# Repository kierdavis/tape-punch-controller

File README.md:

# Tape Punch Controller

This repository contains the source code and CAD designs used for my university third year individual project.

The project involves designing a system that can interface a restored [Teletype BPRE-type High Speed Tape Punch][tapepunch] to a modern computer over USB.

## Repository Layout

- [`/firmware`][repo-firmware]: source code of the firmware running on the microcontroller
- [`/pcb`][repo-pcb]: design files for the PCB used in the device
- [`/mechanical`][repo-mechanical]: design files for various laser-cut parts

[tapepunch]: http://www.computinghistory.org.uk/det/2312/teletype-brpe-20-high-speed-tape-punch/
[repo-firmware]: https://github.com/kierdavis/tape-punch-controller/tree/master/firmware
[repo-pcb]: https://github.com/kierdavis/tape-punch-controller/tree/master/pcb
[repo-mechanical]: https://github.com/kierdavis/tape-punch-controller/tree/master/mechanical

## Branches

Two main Git branches are used with this repository: `master` and `stable`. New development occurs on `master`; when it has been tested and is deemed ready to ship to the client, it is merged into `stable`. `stable` should be a reflection of the version currently in use by the client.

## License

The contents of this repository are licensed under the terms of the MIT license. See the [LICENSE](LICENSE) file for more details.

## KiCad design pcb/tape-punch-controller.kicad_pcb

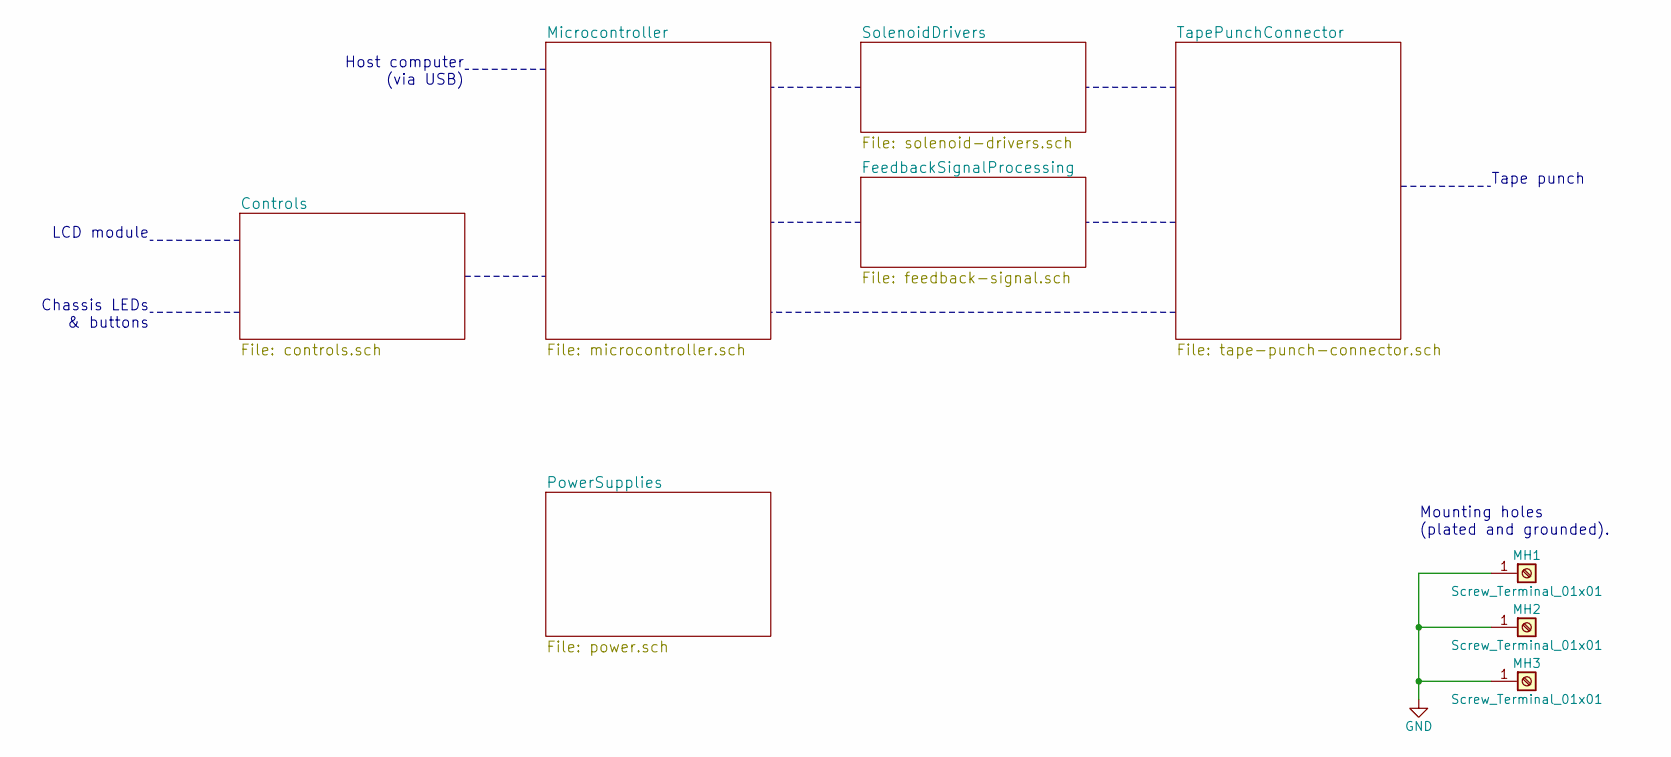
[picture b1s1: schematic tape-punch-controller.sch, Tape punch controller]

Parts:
MH1, MH2, MH3: Screw_Terminal_01x01; MountingHole_4.3mm_M4_Pad

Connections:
GND: MH1.1, MH2.1, MH3.1; also elsewhere on the board

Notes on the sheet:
Mounting holes (plated and grounded).
LCD module
Chassis LEDs & buttons
Host computer (via USB)
Tape punch

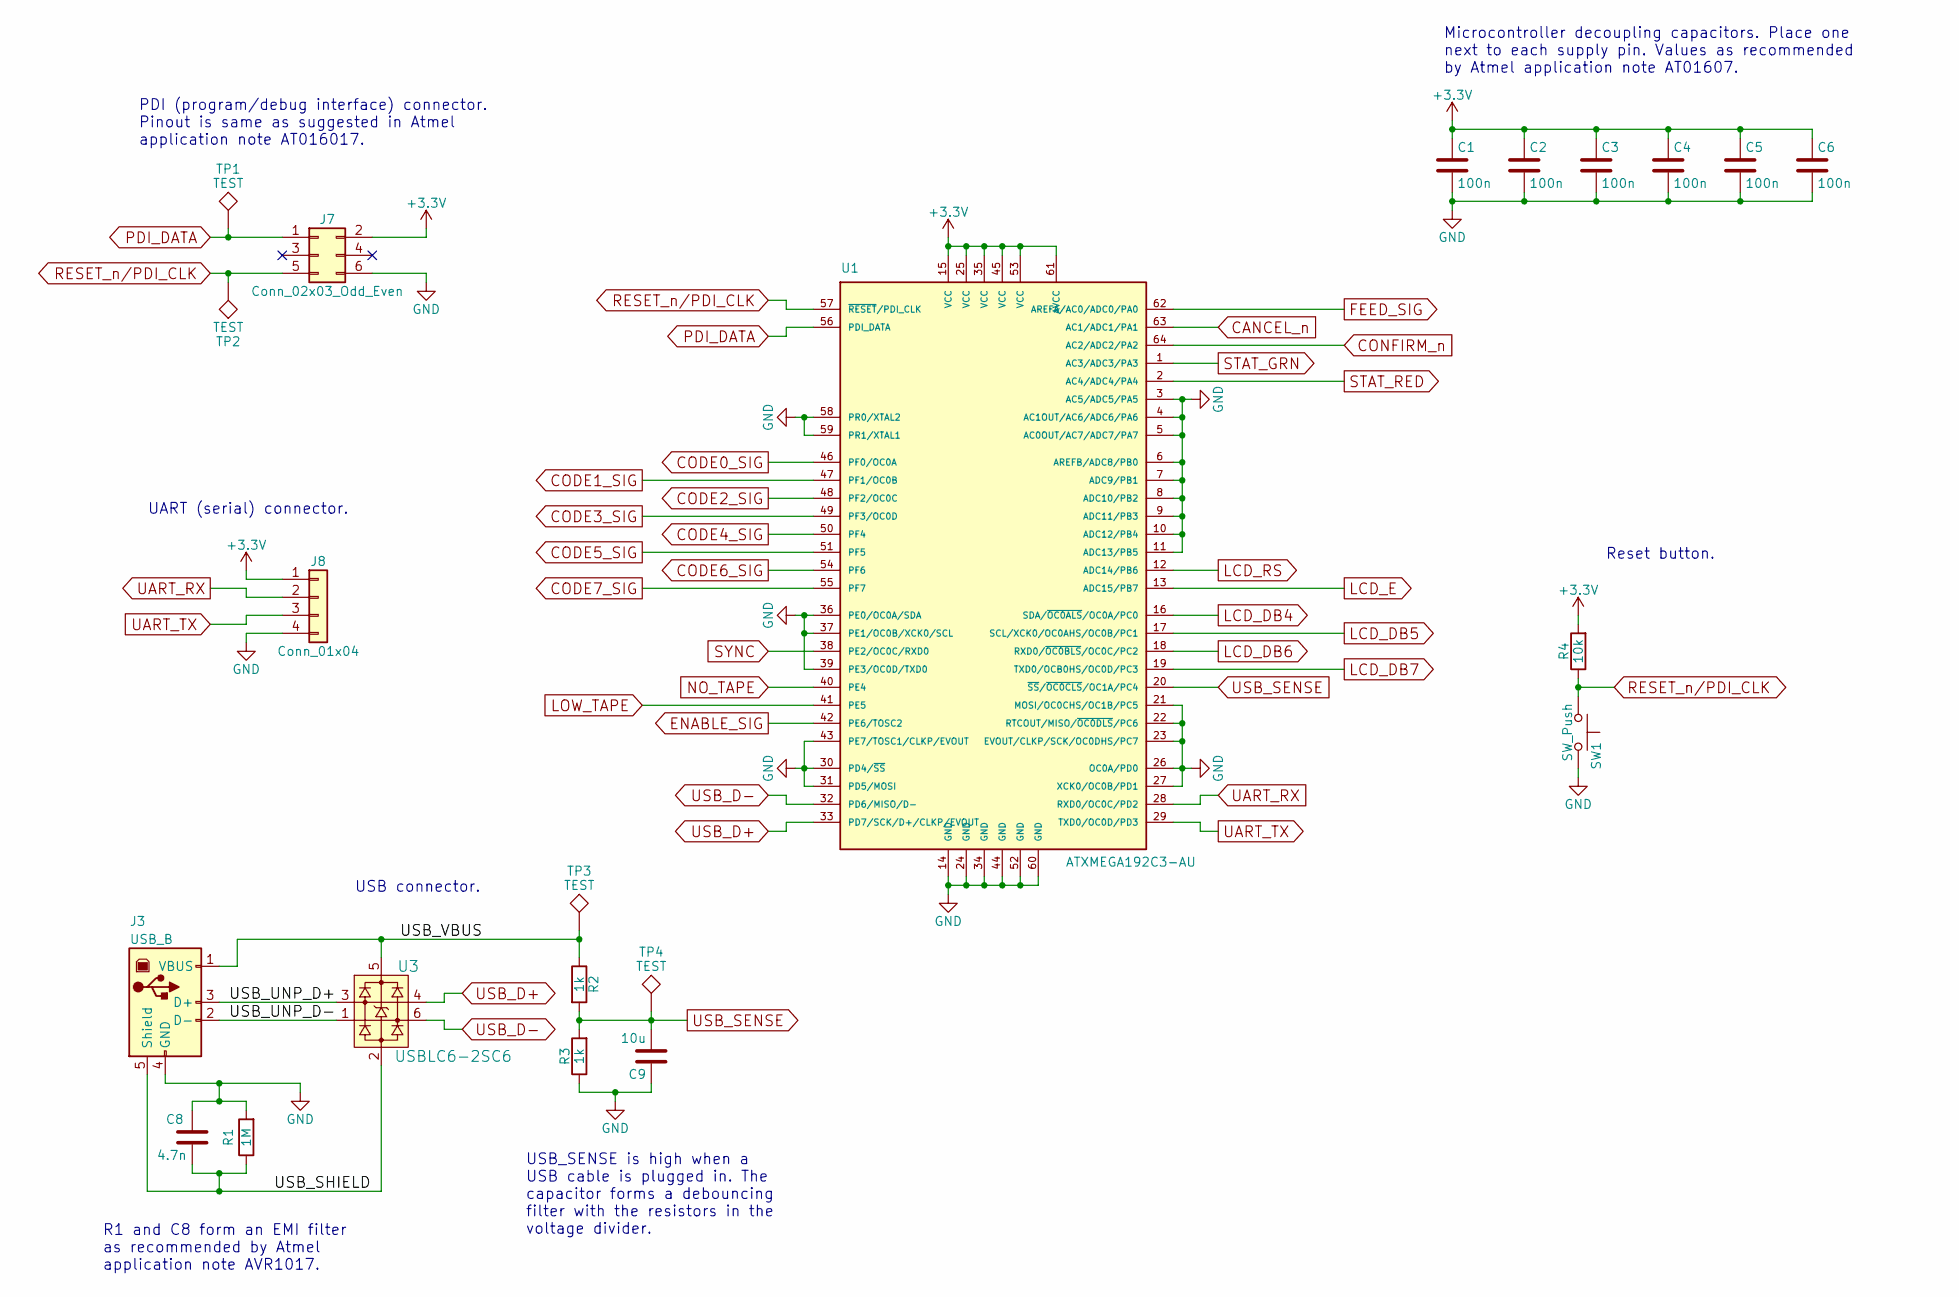
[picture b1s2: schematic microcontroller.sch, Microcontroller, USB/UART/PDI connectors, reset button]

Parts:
C1, C2, C3, C4, C5, C6: 100n; C_0805_HandSoldering
C8: 4.7n; C_0805_HandSoldering
C9: 10u; C_1206_HandSoldering
J3: USB_B; Multicomp_MC32597
J7: Conn_02x03_Odd_Even; Pin_Header_Straight_2x03_Pitch2.54mm
J8: Conn_01x04; Pin_Header_Straight_1x04_Pitch2.54mm
R1: 1M; R_0805_HandSoldering
R2, R3: 1k; R_0805_HandSoldering
R4: 10k; R_0805_HandSoldering
SW1: SW_Push; SW_Tactile_SPST_Angled_PTS645Vx58-2LFS
TP1, TP2, TP3, TP4: TEST; Measurement_Point_Round-SMD-Pad_Small
U1: ATXMEGA192C3-AU; TQFP-64_14x14mm_Pitch0.8mm
U3: USBLC6-2SC6; SOT-23-6_Handsoldering

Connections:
+3V3: C1.1, C2.1, C3.1, C4.1, C5.1, C6.1, J7.2, J8.1, R4.2, U1.15 (VCC), U1.25 (VCC), U1.35 (VCC), U1.45 (VCC), U1.53 (VCC), U1.61 (AVCC); also elsewhere on the board
/Microcontroller/USB_SHIELD: C8.2, J3.5 (Shield), R1.1, U3.2 (GND)
/Microcontroller/USB_UNP_D+: J3.3 (D+), U3.3 (D+)
/Microcontroller/USB_UNP_D-: J3.2 (D-), U3.1 (D-)
/Microcontroller/USB_VBUS: J3.1 (VBUS), R2.1, TP3.1, U3.5 (VBUS)
CANCEL_n: U1.63 (AC1/ADC1/PA1); also elsewhere on the board
CODE0_SIG: U1.46 (PF0/OC0A); also elsewhere on the board
CODE1_SIG: U1.47 (PF1/OC0B); also elsewhere on the board
CODE2_SIG: U1.48 (PF2/OC0C); also elsewhere on the board
CODE3_SIG: U1.49 (PF3/OC0D); also elsewhere on the board
CODE4_SIG: U1.50 (PF4); also elsewhere on the board
CODE5_SIG: U1.51 (PF5); also elsewhere on the board
CODE6_SIG: U1.54 (PF6); also elsewhere on the board
CODE7_SIG: U1.55 (PF7); also elsewhere on the board
CONFIRM_n: U1.64 (AC2/ADC2/PA2); also elsewhere on the board
ENABLE_SIG: U1.42 (PE6/TOSC2); also elsewhere on the board
FEED_SIG: U1.62 (AREFA/AC0/ADC0/PA0); also elsewhere on the board
GND: C1.2, C2.2, C3.2, C4.2, C5.2, C6.2, C8.1, C9.1, J3.4 (GND), J7.6, J8.4, R1.2, R3.1, SW1.2, U1.3 (AC5/ADC5/PA5), U1.4 (AC1OUT/AC6/ADC6/PA6), U1.5 (AC0OUT/AC7/ADC7/PA7), U1.6 (AREFB/ADC8/PB0), U1.7 (ADC9/PB1), U1.8 (ADC10/PB2), U1.9 (ADC11/PB3), U1.10 (ADC12/PB4), U1.11 (ADC13/PB5), U1.14 (GND), U1.21 (MOSI/OC0CHS/OC1B/PC5), U1.22 (RTCOUT/MISO/~OC0DLS~/PC6), U1.23 (EVOUT/CLKP/SCK/OC0DHS/PC7), U1.24 (GND), U1.26 (OC0A/PD0), U1.27 (XCK0/OC0B/PD1), U1.30 (PD4/~SS~), U1.31 (PD5/MOSI), U1.34 (GND), U1.36 (PE0/OC0A/SDA), U1.37 (PE1/OC0B/XCK0/SCL), U1.39 (PE3/OC0D/TXD0), U1.43 (PE7/TOSC1/CLKP/EVOUT), U1.44 (GND), U1.52 (GND), U1.58 (PR0/XTAL2), U1.59 (PR1/XTAL1), U1.60 (GND); also elsewhere on the board
LCD_DB4: U1.16 (SDA/~OC0ALS~/OC0A/PC0); also elsewhere on the board
LCD_DB5: U1.17 (SCL/XCK0/OC0AHS/OC0B/PC1); also elsewhere on the board
LCD_DB6: U1.18 (RXD0/~OC0BLS~/OC0C/PC2); also elsewhere on the board
LCD_DB7: U1.19 (TXD0/OCB0HS/OC0D/PC3); also elsewhere on the board
LCD_E: U1.13 (ADC15/PB7); also elsewhere on the board
LCD_RS: U1.12 (ADC14/PB6); also elsewhere on the board
LOW_TAPE: U1.41 (PE5); also elsewhere on the board
NO_TAPE: U1.40 (PE4); also elsewhere on the board
PDI_DATA: J7.1, TP1.1, U1.56 (PDI_DATA)
RESET_n/PDI_CLK: J7.5, R4.1, SW1.1, TP2.1, U1.57 (~RESET~/PDI_CLK)
STAT_GRN: U1.1 (AC3/ADC3/PA3); also elsewhere on the board
STAT_RED: U1.2 (AC4/ADC4/PA4); also elsewhere on the board
SYNC: U1.38 (PE2/OC0C/RXD0); also elsewhere on the board
UART_RX: J8.2, U1.28 (RXD0/OC0C/PD2)
UART_TX: J8.3, U1.29 (TXD0/OC0D/PD3)
USB_D+: U1.33 (PD7/SCK/D+/CLKP/EVOUT), U3.4 (D+)
USB_D-: U1.32 (PD6/MISO/D-), U3.6 (D-)
USB_SENSE: C9.2, R2.2, R3.2, TP4.1, U1.20 (~SS~/~OC0CLS~/OC1A/PC4)

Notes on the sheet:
Microcontroller decoupling capacitors. Place one next to each supply pin. Values as recommended by Atmel application note AT01607.
UART (serial) connector.
PDI (program/debug interface) connector. Pinout is same as suggested in Atmel application note AT016017.
USB connector.
USB_SENSE is high when a USB cable is plugged in. The capacitor forms a debouncing filter with the resistors in the voltage divider.
R1 and C8 form an EMI filter as recommended by Atmel application note AVR1017.
Reset button.

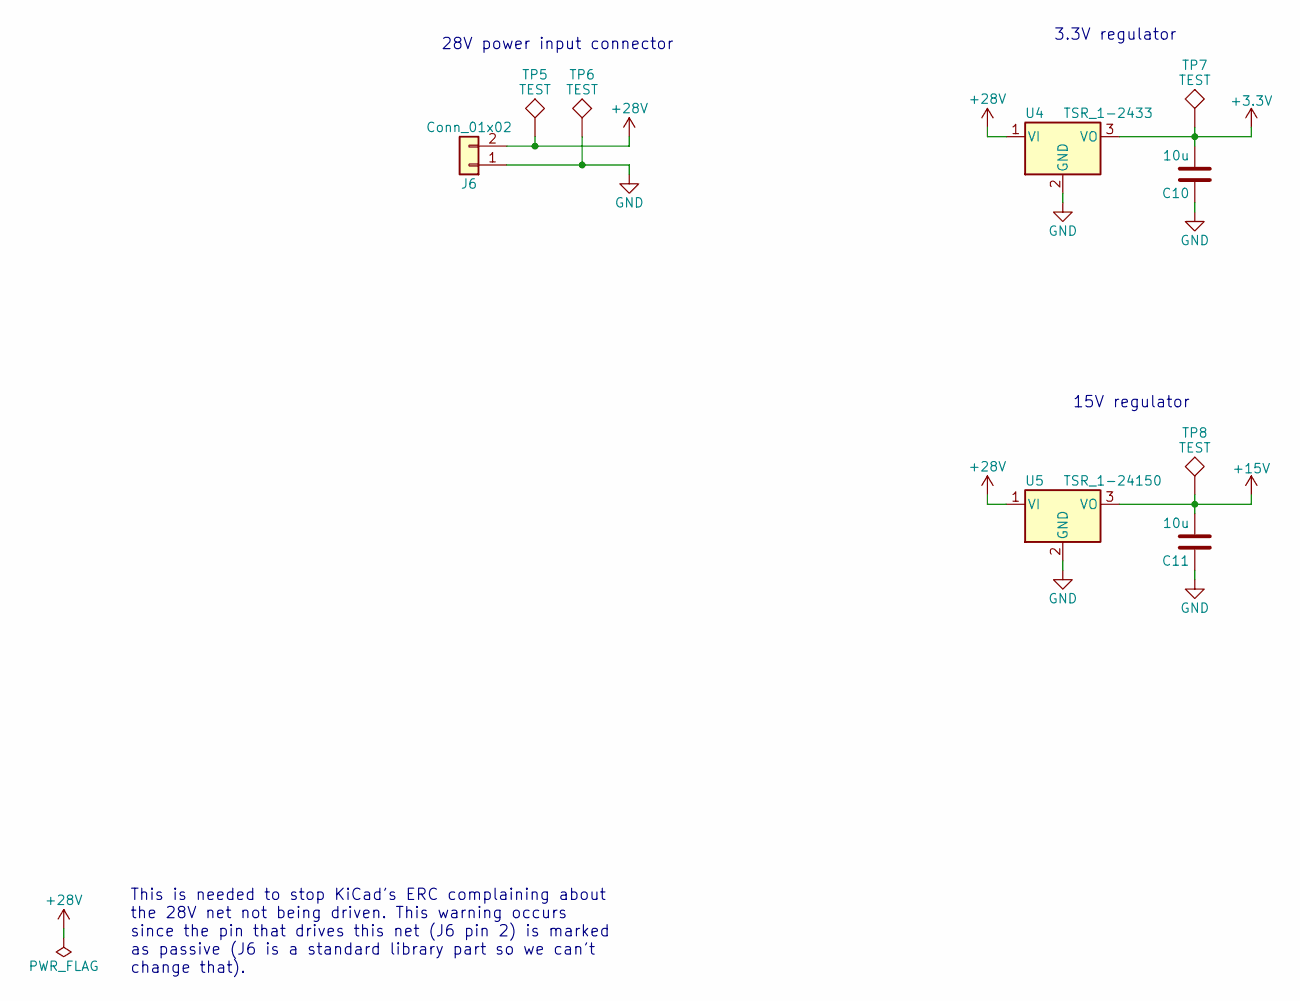
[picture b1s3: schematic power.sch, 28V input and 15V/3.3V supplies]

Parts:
C10, C11: 10u; C_1206_HandSoldering
J6: Conn_01x02; Multicomp_MC000048
TP5, TP6, TP7, TP8: TEST; Measurement_Point_Round-SMD-Pad_Small
U4: TSR_1-2433; TO-220-3_Vertical
U5: TSR_1-24150; TO-220-3_Vertical

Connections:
+3V3: C10.2, TP7.1, U4.3 (VO); also elsewhere on the board
+15V: C11.2, TP8.1, U5.3 (VO); also elsewhere on the board
+28V: J6.2, TP5.1, U4.1 (VI), U5.1 (VI); also elsewhere on the board
GND: C10.1, C11.1, J6.1, TP6.1, U4.2 (GND), U5.2 (GND); also elsewhere on the board

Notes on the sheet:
28V power input connector
3.3V regulator
15V regulator
This is needed to stop KiCad's ERC complaining about the 28V net not being driven. This warning occurs since the pin that drives this net (J6 pin 2) is marked as passive (J6 is a standard library part so we can't change that).

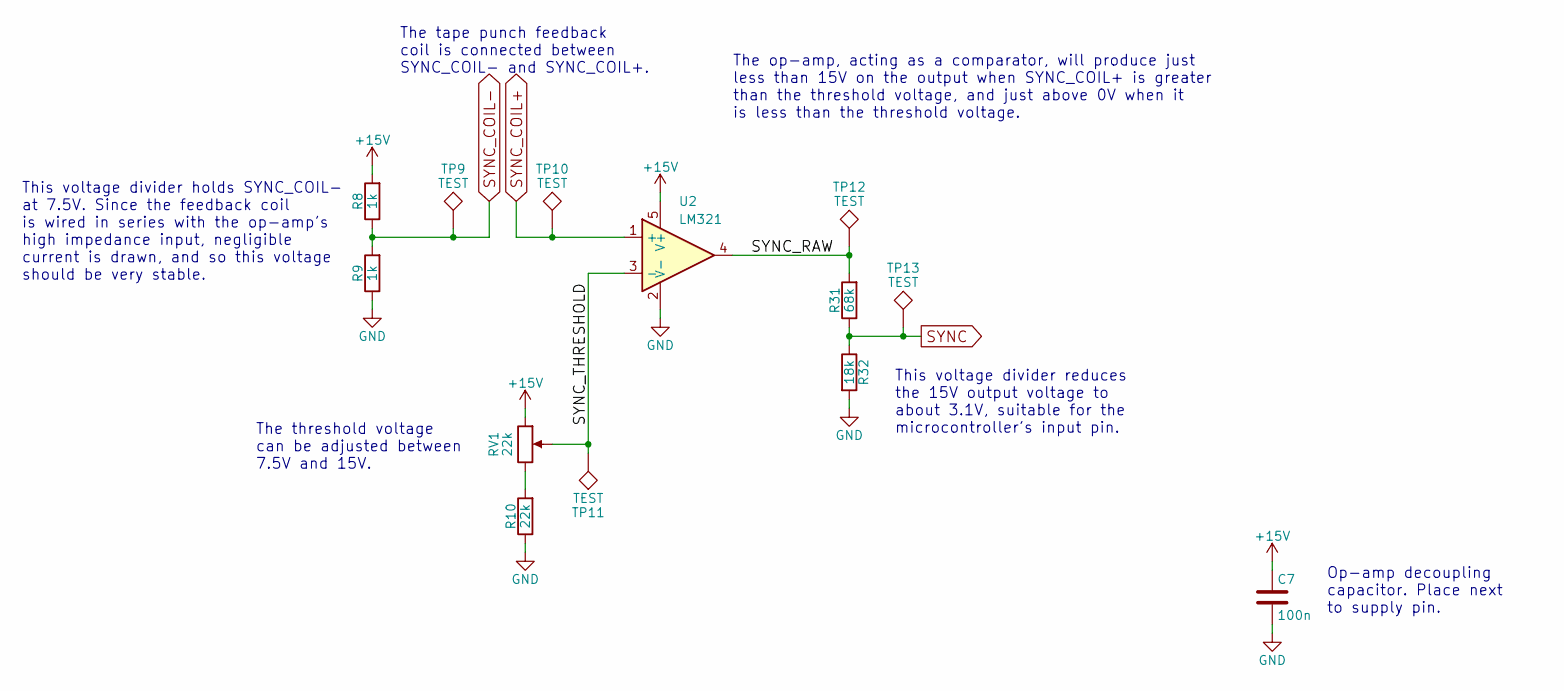
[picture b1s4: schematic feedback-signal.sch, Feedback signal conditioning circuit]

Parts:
C7: 100n; C_0805_HandSoldering
R8, R9: 1k; R_0805_HandSoldering
R10: 22k; R_0805_HandSoldering
R31: 68k; R_0805_HandSoldering
R32: 18k; R_0805_HandSoldering
RV1: 22k; Citec_CB10LV103M
TP9, TP10, TP11, TP12, TP13: TEST; Measurement_Point_Round-SMD-Pad_Small
U2: LM321; SOT-23-5_HandSoldering

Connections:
+15V: C7.1, R8.2, RV1.1, U2.5 (V+); also elsewhere on the board
/FeedbackSignalProcessing/SYNC_RAW: R31.2, TP12.1, U2.4
/FeedbackSignalProcessing/SYNC_THRESHOLD: RV1.2, TP11.1, U2.3 (-)
GND: C7.2, R9.1, R10.1, R32.2, U2.2 (V-); also elsewhere on the board
unnamed: R10.2, RV1.3
SYNC: R31.1, R32.1, TP13.1; also elsewhere on the board
SYNC_COIL+: TP10.1, U2.1 (+); also elsewhere on the board
SYNC_COIL-: R8.1, R9.2, TP9.1; also elsewhere on the board

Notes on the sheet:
Op-amp decoupling capacitor. Place next to supply pin.
The tape punch feedback coil is connected between SYNC_COIL- and SYNC_COIL+.
This voltage divider holds SYNC_COIL- at 7.5V. Since the feedback coil is wired in series with the op-amp's high impedance input, negligible current is drawn, and so this voltage should be very stable.
The threshold voltage can be adjusted between 7.5V and 15V.
The op-amp, acting as a comparator, will produce just less than 15V on the output when SYNC_COIL+ is greater than the threshold voltage, and just above 0V when it is less than the threshold voltage.
This voltage divider reduces the 15V output voltage to about 3.1V, suitable for the microcontroller's input pin.

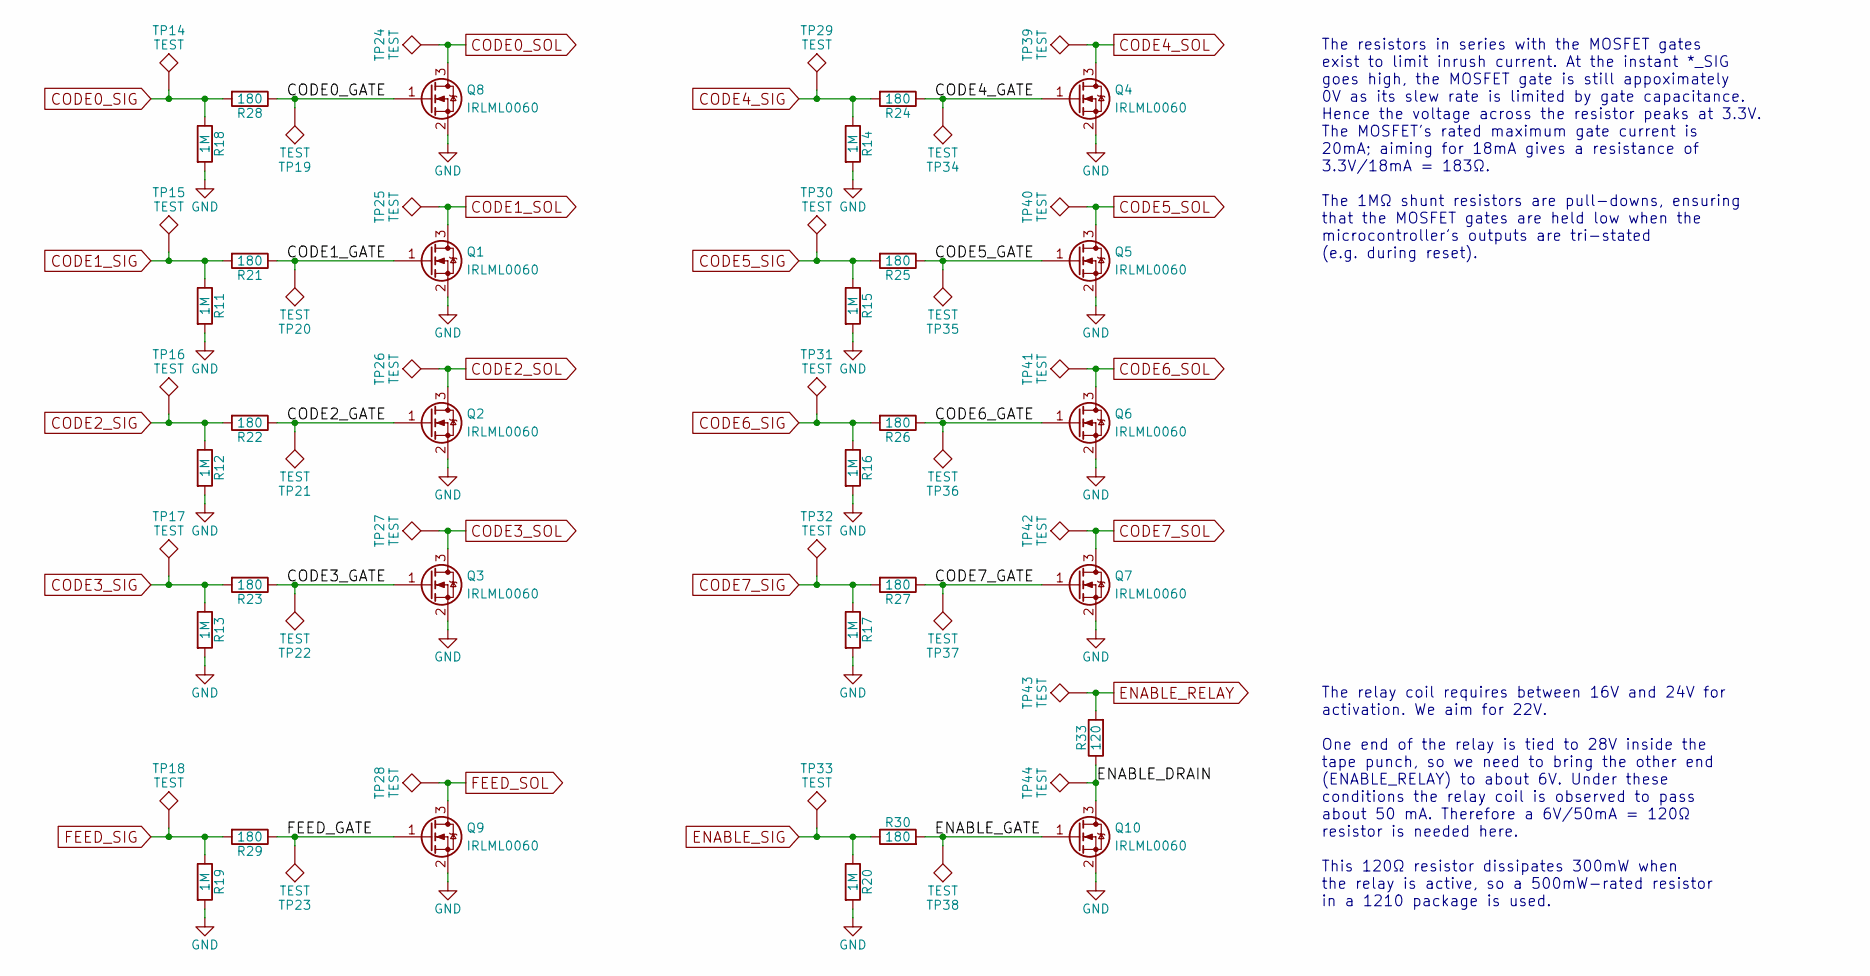
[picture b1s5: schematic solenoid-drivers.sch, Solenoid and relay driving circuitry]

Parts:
Q1, Q2, Q3, Q4, Q5, Q6, Q7, Q8, Q9, Q10: IRLML0060; SOT-23_Handsoldering
R11, R12, R13, R14, R15, R16, R17, R18, R19, R20: 1M; R_0805_HandSoldering
R21, R22, R23, R24, R25, R26, R27, R28, R29, R30: 180; R_0805_HandSoldering
R33: 120; R_1210_HandSoldering
TP14, TP15, TP16, TP17, TP18, TP19, TP20, TP21, TP22, TP23, TP24, TP25, TP26, TP27, TP28, TP29, TP30, TP31, TP32, TP33, TP34, TP35, TP36, TP37, TP38, TP39, TP40, TP41, TP42, TP43, TP44: TEST; Measurement_Point_Round-SMD-Pad_Small

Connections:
/SolenoidDrivers/CODE0_GATE: Q8.1 (G), R28.1, TP19.1
/SolenoidDrivers/CODE1_GATE: Q1.1 (G), R21.1, TP20.1
/SolenoidDrivers/CODE2_GATE: Q2.1 (G), R22.1, TP21.1
/SolenoidDrivers/CODE3_GATE: Q3.1 (G), R23.1, TP22.1
/SolenoidDrivers/CODE4_GATE: Q4.1 (G), R24.1, TP34.1
/SolenoidDrivers/CODE5_GATE: Q5.1 (G), R25.1, TP35.1
/SolenoidDrivers/CODE6_GATE: Q6.1 (G), R26.1, TP36.1
/SolenoidDrivers/CODE7_GATE: Q7.1 (G), R27.1, TP37.1
/SolenoidDrivers/ENABLE_DRAIN: Q10.3 (D), R33.1, TP44.1
/SolenoidDrivers/ENABLE_GATE: Q10.1 (G), R30.2, TP38.1
/SolenoidDrivers/FEED_GATE: Q9.1 (G), R29.1, TP23.1
CODE0_SIG: R18.1, R28.2, TP14.1; also elsewhere on the board
CODE0_SOL: Q8.3 (D), TP24.1; also elsewhere on the board
CODE1_SIG: R11.1, R21.2, TP15.1; also elsewhere on the board
CODE1_SOL: Q1.3 (D), TP25.1; also elsewhere on the board
CODE2_SIG: R12.1, R22.2, TP16.1; also elsewhere on the board
CODE2_SOL: Q2.3 (D), TP26.1; also elsewhere on the board
CODE3_SIG: R13.1, R23.2, TP17.1; also elsewhere on the board
CODE3_SOL: Q3.3 (D), TP27.1; also elsewhere on the board
CODE4_SIG: R14.1, R24.2, TP29.1; also elsewhere on the board
CODE4_SOL: Q4.3 (D), TP39.1; also elsewhere on the board
CODE5_SIG: R15.1, R25.2, TP30.1; also elsewhere on the board
CODE5_SOL: Q5.3 (D), TP40.1; also elsewhere on the board
CODE6_SIG: R16.1, R26.2, TP31.1; also elsewhere on the board
CODE6_SOL: Q6.3 (D), TP41.1; also elsewhere on the board
CODE7_SIG: R17.1, R27.2, TP32.1; also elsewhere on the board
CODE7_SOL: Q7.3 (D), TP42.1; also elsewhere on the board
ENABLE_RELAY: R33.2, TP43.1; also elsewhere on the board
ENABLE_SIG: R20.1, R30.1, TP33.1; also elsewhere on the board
FEED_SIG: R19.1, R29.2, TP18.1; also elsewhere on the board
FEED_SOL: Q9.3 (D), TP28.1; also elsewhere on the board
GND: Q1.2 (S), Q2.2 (S), Q3.2 (S), Q4.2 (S), Q5.2 (S), Q6.2 (S), Q7.2 (S), Q8.2 (S), Q9.2 (S), Q10.2 (S), R11.2, R12.2, R13.2, R14.2, R15.2, R16.2, R17.2, R18.2, R19.2, R20.2; also elsewhere on the board

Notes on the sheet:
The resistors in series with the MOSFET gates exist to limit inrush current. At the instant *_SIG goes high, the MOSFET gate is still appoximately 0V as its slew rate is limited by gate capacitance. Hence the voltage across the resistor peaks at 3.3V. The MOSFET's rated maximum gate current is 20mA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
The relay coil requires between 16V and 24V for activation. We aim for 22V. One end of the relay is tied to 28V inside the tape punch, so we need to bring the other end (ENABLE_RELAY) to about 6V. Under these conditions the relay coil is observed to pass about 50 mA. Therefore a 6V/50mA = 120Ω resi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

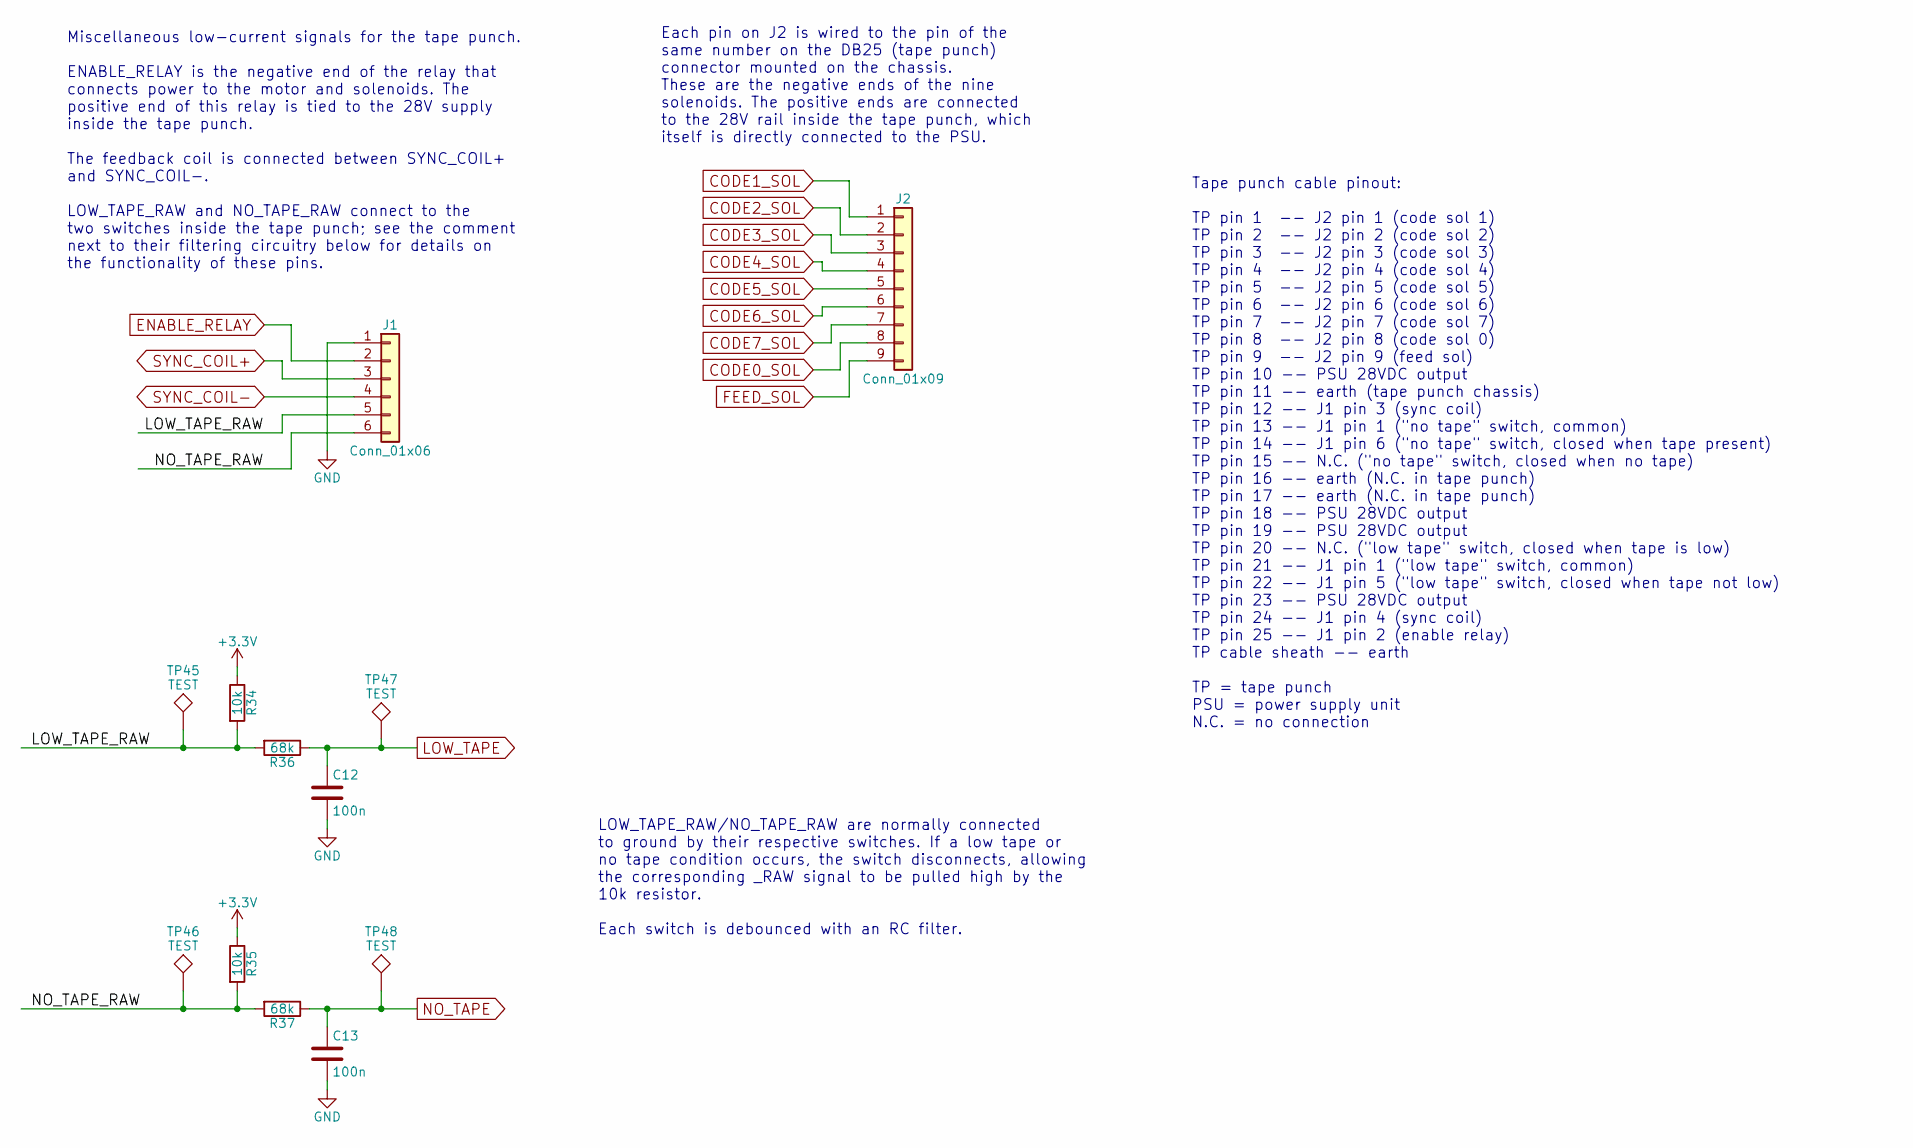
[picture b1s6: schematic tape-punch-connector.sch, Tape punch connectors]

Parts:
C12, C13: 100n; C_0805_HandSoldering
J1: Conn_01x06; Amphenol_T821106A1S100CEU
J2: Conn_01x09; Weidmuller_1234610000
R34, R35: 10k; R_0805_HandSoldering
R36, R37: 68k; R_0805_HandSoldering
TP45, TP46, TP47, TP48: TEST; Measurement_Point_Round-SMD-Pad_Small

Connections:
+3V3: R34.1, R35.1; also elsewhere on the board
/TapePunchConnector/LOW_TAPE_RAW: J1.5, R34.2, R36.2, TP45.1
/TapePunchConnector/NO_TAPE_RAW: J1.6, R35.2, R37.2, TP46.1
CODE0_SOL: J2.8; also elsewhere on the board
CODE1_SOL: J2.1; also elsewhere on the board
CODE2_SOL: J2.2; also elsewhere on the board
CODE3_SOL: J2.3; also elsewhere on the board
CODE4_SOL: J2.4; also elsewhere on the board
CODE5_SOL: J2.5; also elsewhere on the board
CODE6_SOL: J2.6; also elsewhere on the board
CODE7_SOL: J2.7; also elsewhere on the board
ENABLE_RELAY: J1.2; also elsewhere on the board
FEED_SOL: J2.9; also elsewhere on the board
GND: C12.2, C13.2, J1.1; also elsewhere on the board
LOW_TAPE: C12.1, R36.1, TP47.1; also elsewhere on the board
NO_TAPE: C13.1, R37.1, TP48.1; also elsewhere on the board
SYNC_COIL+: J1.3; also elsewhere on the board
SYNC_COIL-: J1.4; also elsewhere on the board

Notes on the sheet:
LOW_TAPE_RAW/NO_TAPE_RAW are normally connected to ground by their respective switches. If a low tape or no tape condition occurs, the switch disconnects, allowing the corresponding _RAW signal to be pulled high by the 10k resistor. Each switch is debounced with an RC filter.
Each pin on J2 is wired to the pin of the same number on the DB25 (tape punch) connector mounted on the chassis. These are the negative ends of the nine solenoids. The positive ends are connected to the 28V rail inside the tape punch, which itself is directly connected to the PSU.
Tape punch cable pinout: TP pin 1 -- J2 pin 1 (code sol 1) TP pin 2 -- J2 pin 2 (code sol 2) TP pin 3 -- J2 pin 3 (code sol 3) TP pin 4 -- J2 pin 4 (code sol 4) TP pin 5 -- J2 pin 5 (code sol 5) TP pin 6 -- J2 pin 6 (code sol 6) TP pin 7 -- J2 pin 7 (code sol 7) TP pin 8 -- J2 pin 8 (code sol 0) TP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
Miscellaneous low-current signals for the tape punch. ENABLE_RELAY is the negative end of the relay that connects power to the motor and solenoids. The positive end of this relay is tied to the 28V supply inside the tape punch. The feedback coil is connected between SYNC_COIL+ and SYNC_COIL-. LOW_T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

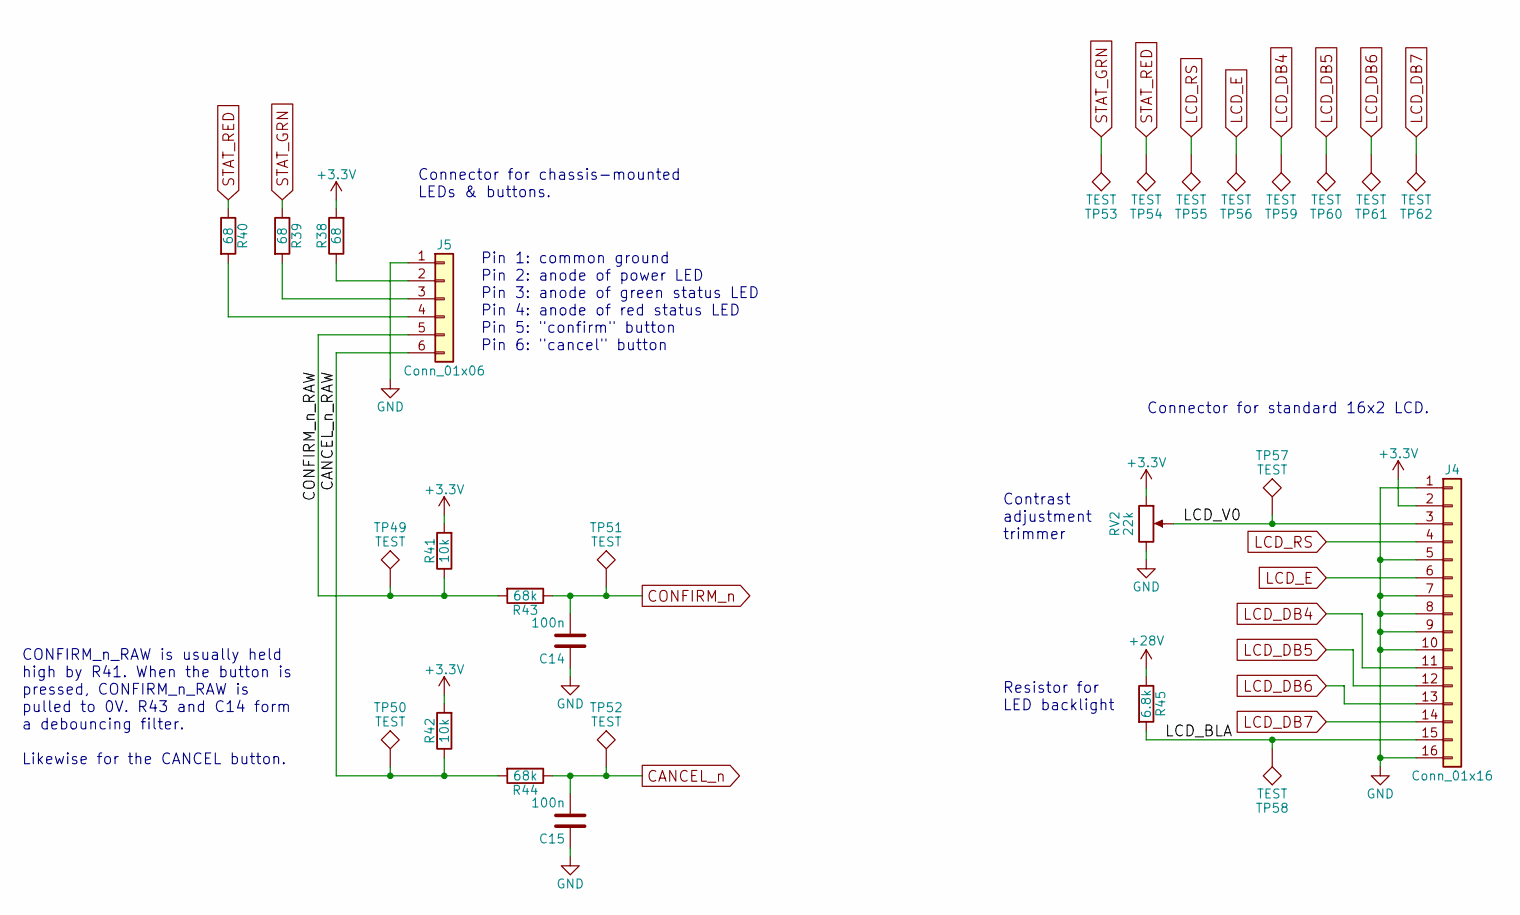
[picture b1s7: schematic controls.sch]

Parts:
C14, C15: 100n; C_0805_HandSoldering
J4: Conn_01x16; Amphenol_T821116A1S100CEU
J5: Conn_01x06; Amphenol_T821106A1S100CEU
R38, R39, R40: 68; R_0805_HandSoldering
R41, R42: 10k; R_0805_HandSoldering
R43, R44: 68k; R_0805_HandSoldering
R45: 6.8k; R_0805_HandSoldering
RV2: 22k; Citec_CB10LV103M
TP49, TP50, TP51, TP52, TP53, TP54, TP55, TP56, TP57, TP58, TP59, TP60, TP61, TP62: TEST; Measurement_Point_Round-SMD-Pad_Small

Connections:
+3V3: J4.2, R38.2, R41.2, R42.2, RV2.1; also elsewhere on the board
+28V: R45.1; also elsewhere on the board
/Controls/CANCEL_n_RAW: J5.6, R42.1, R44.2, TP50.1
/Controls/CONFIRM_n_RAW: J5.5, R41.1, R43.2, TP49.1
/Controls/LCD_BLA: J4.15, R45.2, TP58.1
/Controls/LCD_V0: J4.3, RV2.2, TP57.1
CANCEL_n: C15.2, R44.1, TP52.1; also elsewhere on the board
CONFIRM_n: C14.2, R43.1, TP51.1; also elsewhere on the board
GND: C14.1, C15.1, J4.1, J4.5, J4.7, J4.8, J4.9, J4.10, J4.16, J5.1, RV2.3; also elsewhere on the board
LCD_DB4: J4.11, TP59.1; also elsewhere on the board
LCD_DB5: J4.12, TP60.1; also elsewhere on the board
LCD_DB6: J4.13, TP61.1; also elsewhere on the board
LCD_DB7: J4.14, TP62.1; also elsewhere on the board
LCD_E: J4.6, TP56.1; also elsewhere on the board
LCD_RS: J4.4, TP55.1; also elsewhere on the board
unnamed: J5.2, R38.1
unnamed: J5.3, R39.2
unnamed: J5.4, R40.2
STAT_GRN: R39.1, TP53.1; also elsewhere on the board
STAT_RED: R40.1, TP54.1; also elsewhere on the board

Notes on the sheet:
Contrast adjustment trimmer
Resistor for LED backlight
Connector for standard 16x2 LCD.
Connector for chassis-mounted LEDs & buttons.
Pin 1: common ground Pin 2: anode of power LED Pin 3: anode of green status LED Pin 4: anode of red status LED Pin 5: "confirm" button Pin 6: "cancel" button
CONFIRM_n_RAW is usually held high by R41. When the button is pressed, CONFIRM_n_RAW is pulled to 0V. R43 and C14 form a debouncing filter. Likewise for the CANCEL button.

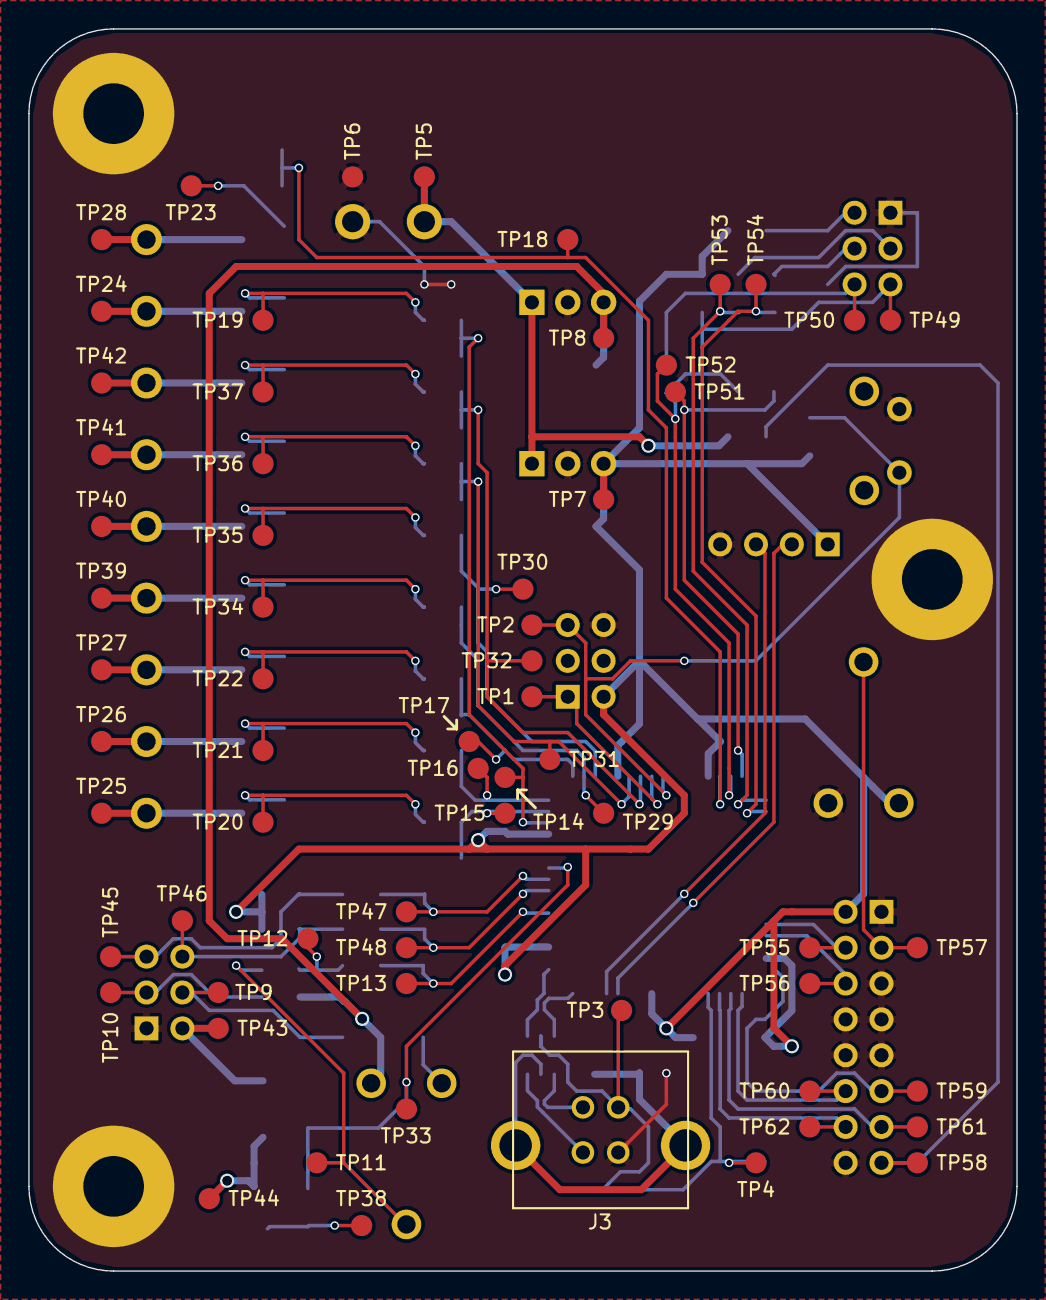
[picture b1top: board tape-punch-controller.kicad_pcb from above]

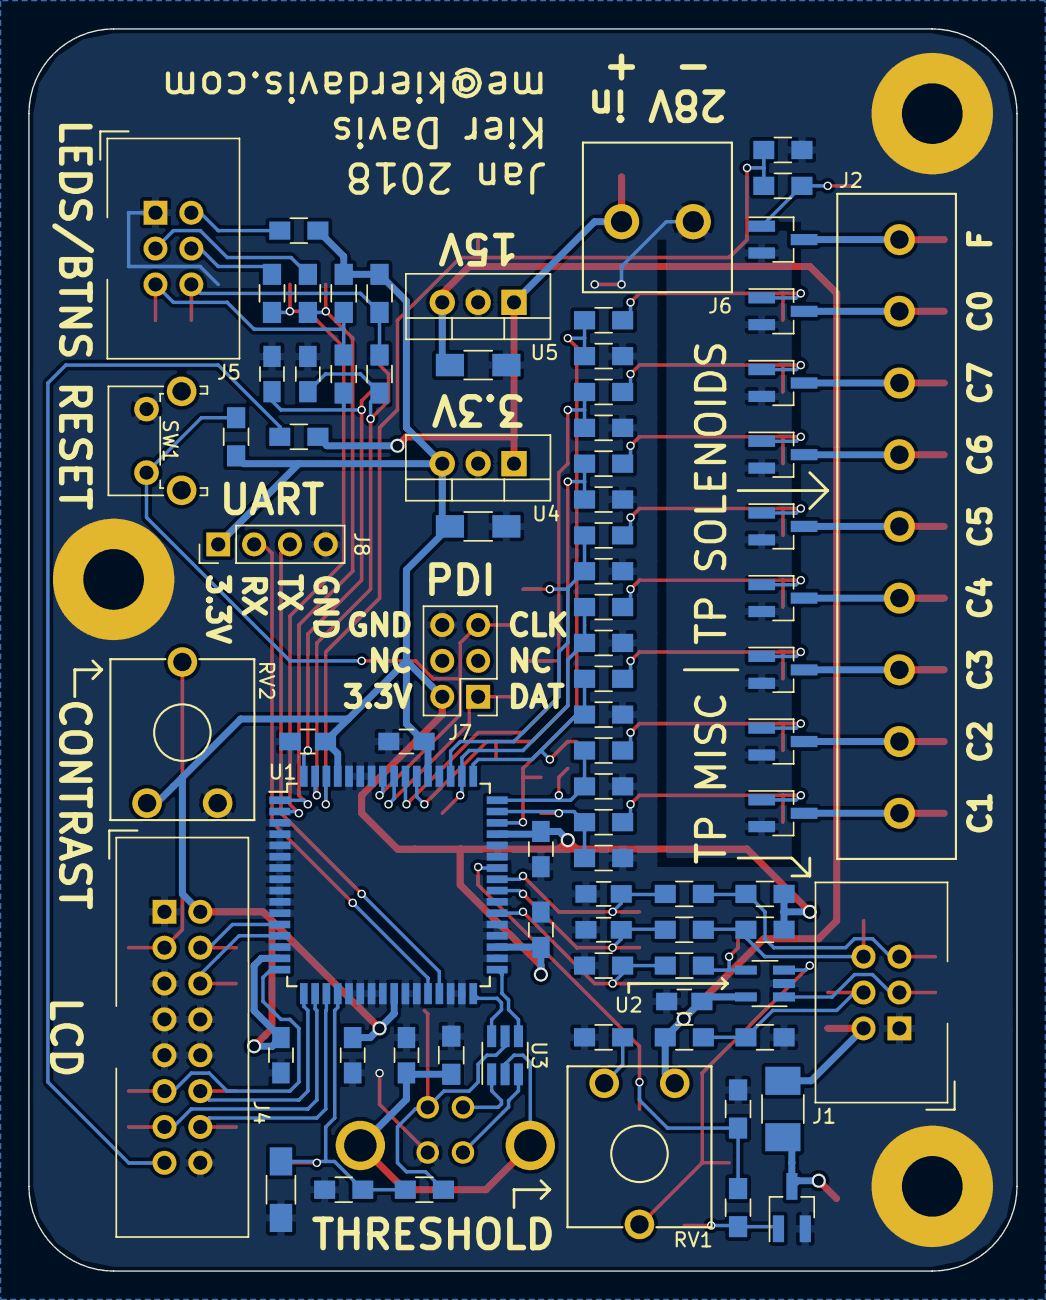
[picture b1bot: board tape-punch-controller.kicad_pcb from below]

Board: 2 copper layers, 70.0 x 88.0 mm, 148 parts (85 on the bottom side), 73 nets.
